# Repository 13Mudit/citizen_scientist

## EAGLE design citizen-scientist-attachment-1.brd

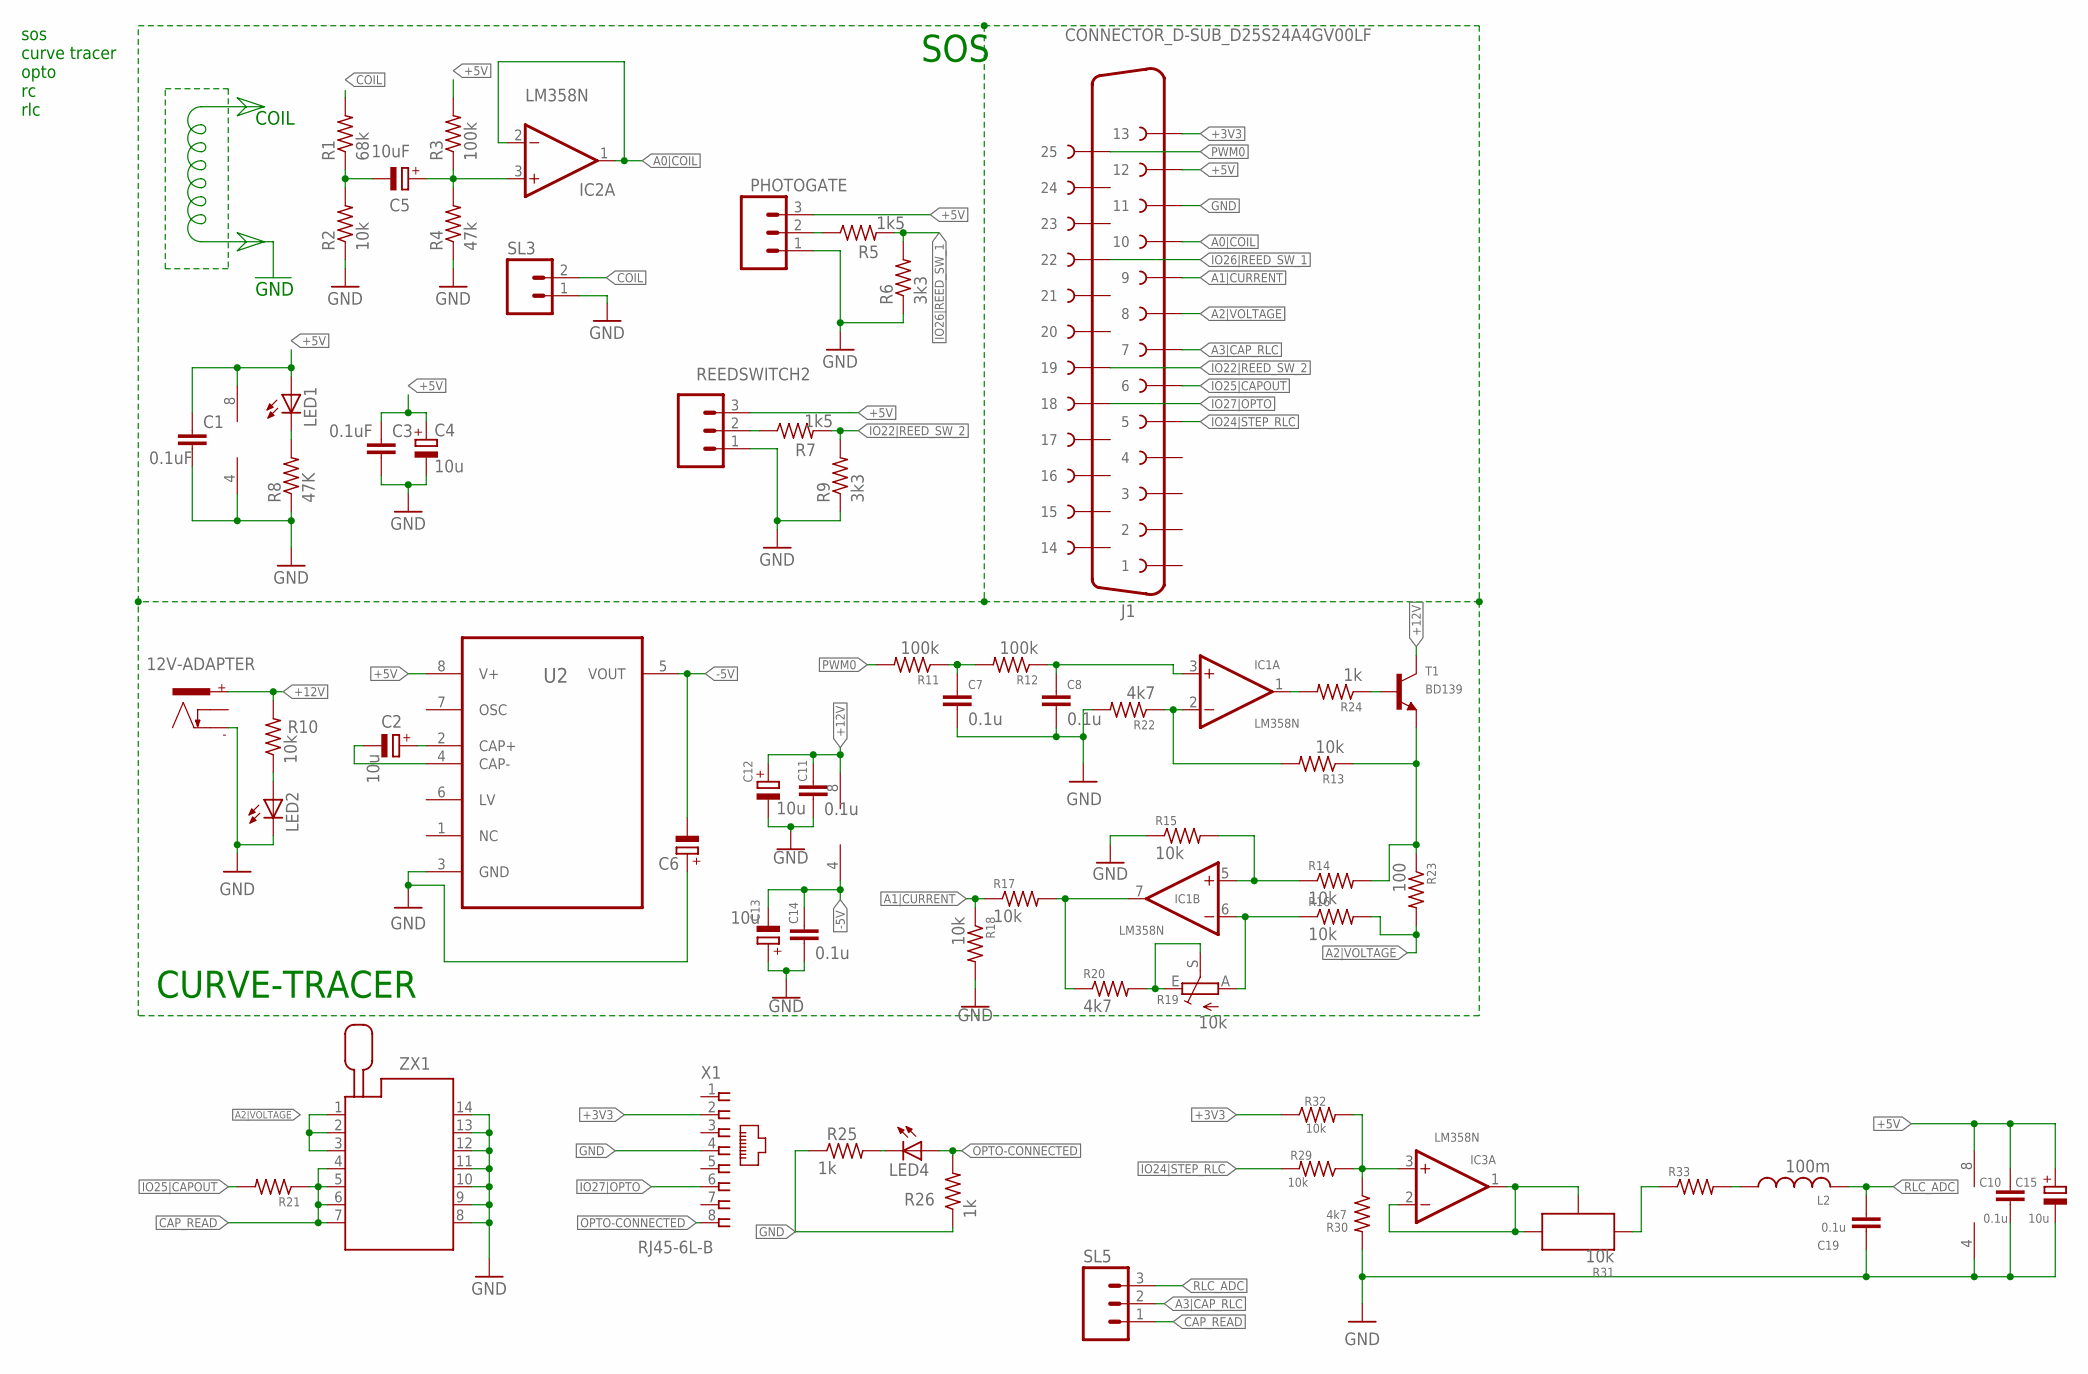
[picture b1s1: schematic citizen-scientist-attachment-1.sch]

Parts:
12V-ADAPTER: POWER_CON; NEB21R
C1, C3: 0.1uF; C025-025X050
C2, C12, C13, C15: 10u; TT2D5
C4: 10u; E2,5-6
C5: 10uF; E2,5-6
C6: CPOL-EUTT2D5; TT2D5
C7, C8, C10, C11, C14, C19: 0.1u; C025-025X050
IC1, IC2, IC3: LM358N; DIL08
J1: CONNECTOR_D-SUB_D25S24A4GV00LF
L2: 100m; 6000-XXXX-RC
LED1, LED2, LED4: LED3MM
PHOTOGATE: M03; 03P
R1: 68k; 0204/7
R2, R10, R29: 10k; 0204/7
R3, R11, R12: 100k; 0204/7
R4: 47k; 0204/7
R5, R7: 1k5; 0204/7
R6, R9: 3k3; 0204/7
R8: 47K; 0204/7
R13, R14, R15, R16, R17, R18, R32: 10k; 0207/10
R19, R31: 10k; RJ9W
R20: 4k7; 0204/7
R21, R33: R-US_0204/7; 0204/7
R22, R30: 4k7; 0207/10
R23: 100; 0207/10
R24, R25, R26: 1k; 0204/7
REEDSWITCH2: M03; 03P
SL3: M02; 02P
SL5: M03; 03P
T1: BD139; TO126
U2: ICL7660CPAZ_ICL7660CPAZ; ICL7660CPAZ_DIP254P762X533-8
X1: RJ45-6L-B; RJ45-NO-SHIELD
ZX1: 214-3339-00-0602J

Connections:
+3V3: J1.P$13 (13), R32.1, X1.2
+5V: C1.1, C3.1, C4.+, C10.1, C15.+, IC2.8 (V+), IC3.8 (V+), J1.P$14 (12), LED1.A, PHOTOGATE.3, R3.2, REEDSWITCH2.3, U2.8 (V+)
+12V: 12V-ADAPTER.+, C11.1, C12.+, IC1.8 (V+), R10.2, T1.2 (C)
-5V: C6.-, C13.-, C14.1, IC1.4 (V-), U2.5 (VOUT)
A0|COIL: IC2.1 (OUT), IC2.2 (-IN), J1.P$16 (10)
A1|CURRENT: J1.P$17 (9), R17.1, R18.1
A2|VOLTAGE: J1.P$18 (8), R16.2, R23.2, ZX1.1, ZX1.2, ZX1.3
A3|CAP_RLC: J1.P$19 (7), SL5.2
CAP_READ: R21.1, SL5.1, ZX1.4, ZX1.5, ZX1.6, ZX1.7
CLAMP_SIGNAL: C5.+, IC2.3 (+IN), R3.1, R4.2
COIL: R1.2, SL3.2
GND: 12V-ADAPTER.-, C1.2, C3.2, C4.-, C6.+, C7.2, C8.2, C10.2, C11.2, C12.-, C13.+, C14.2, C15.-, C19.2, IC2.4 (V-), IC3.4 (V-), J1.P$15 (11), LED2.K (C), PHOTOGATE.1, R2.1, R4.1, R6.1, R8.1, R9.1, R15.1, R18.2, R22.2, R25.1, R26.1, R30.2, REEDSWITCH2.1, SL3.1, U2.3 (GND), X1.4, ZX1.8, ZX1.9, ZX1.10, ZX1.11, ZX1.12, ZX1.13, ZX1.14
IO22|REED_SW_2: J1.P$7 (19), R7.2, R9.2
IO24|STEP_RLC: J1.P$21 (5), R29.2
IO25|CAPOUT: J1.P$20 (6), R21.2
IO26|REED_SW_1: J1.P$4 (22), R5.2, R6.2
IO27|OPTO: J1.P$8 (18), X1.6
unnamed: C5.-, R1.1, R2.2
unnamed: PHOTOGATE.2, R5.1
unnamed: R7.1, REEDSWITCH2.2
unnamed: LED1.K (C), R8.2
unnamed: C2.+, U2.2 (CAP+)
unnamed: C2.-, U2.4 (CAP-)
unnamed: C7.1, R11.1, R12.2
unnamed: LED2.A, R10.1
unnamed: IC1.1 (OUT), R24.2
unnamed: R24.1, T1.3 (B)
unnamed: C8.1, IC1.3 (+IN), R12.1
unnamed: IC1.2 (-IN), R13.2, R22.1
unnamed: IC1.5 (+IN), R14.1, R15.2
unnamed: IC1.6 (-IN), R16.1, R19.A
unnamed: R13.1, R14.2, R23.1, T1.1 (E)
unnamed: R19.E, R19.S, R20.2
unnamed: IC1.7 (OUT), R17.2, R20.1
unnamed: LED4.K (C), R25.2
unnamed: IC3.3 (+IN), R29.1, R30.1, R32.2
unnamed: IC3.1 (OUT), IC3.2 (-IN), R31.A, R31.S
unnamed: R31.E, R33.1
unnamed: L2.1, R33.2
OPTO-CONNECTED: LED4.A, R26.2, X1.8
PWM0: J1.P$1 (25), R11.2
PWM1: J1.P$6 (20)
RLC_ADC: C19.1, L2.2, SL5.3

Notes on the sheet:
COIL
GND
sos curve tracer opto rc rlc
SOS
CURVE-TRACER

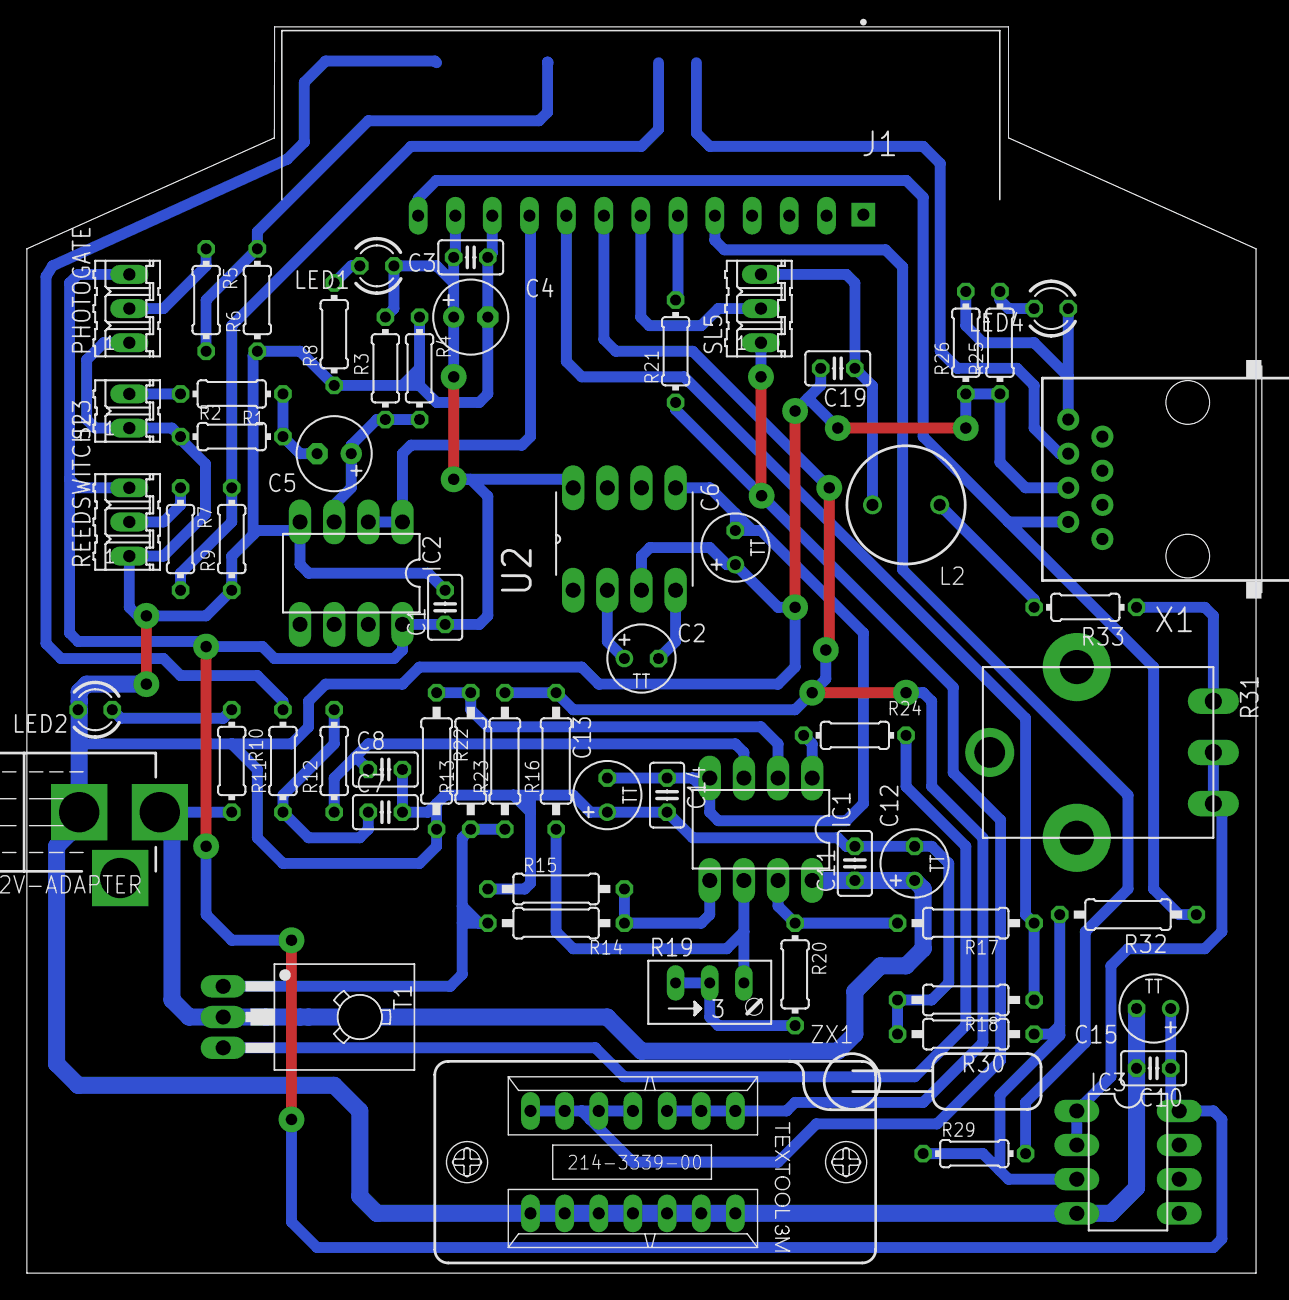
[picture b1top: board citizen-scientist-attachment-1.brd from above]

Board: 2 copper layers, 91.9 x 92.7 mm, 63 parts (0 on the bottom side), 42 nets.

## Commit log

2023-02-03 Working code, only single shot capture after trigger
2023-02-04 Stream and single shot function added, no graph output
2023-02-09 Multi exp running
2023-02-11 With GUI Working
2023-02-15 fully Working server for SOS, photogate and RLC curve

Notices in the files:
parts and their libraries:
SparkFun-PowerSymbols: Licensing: Creative Commons ShareAlike 4.0 International - https://creativecommons.org/licenses/by-sa/4.0
